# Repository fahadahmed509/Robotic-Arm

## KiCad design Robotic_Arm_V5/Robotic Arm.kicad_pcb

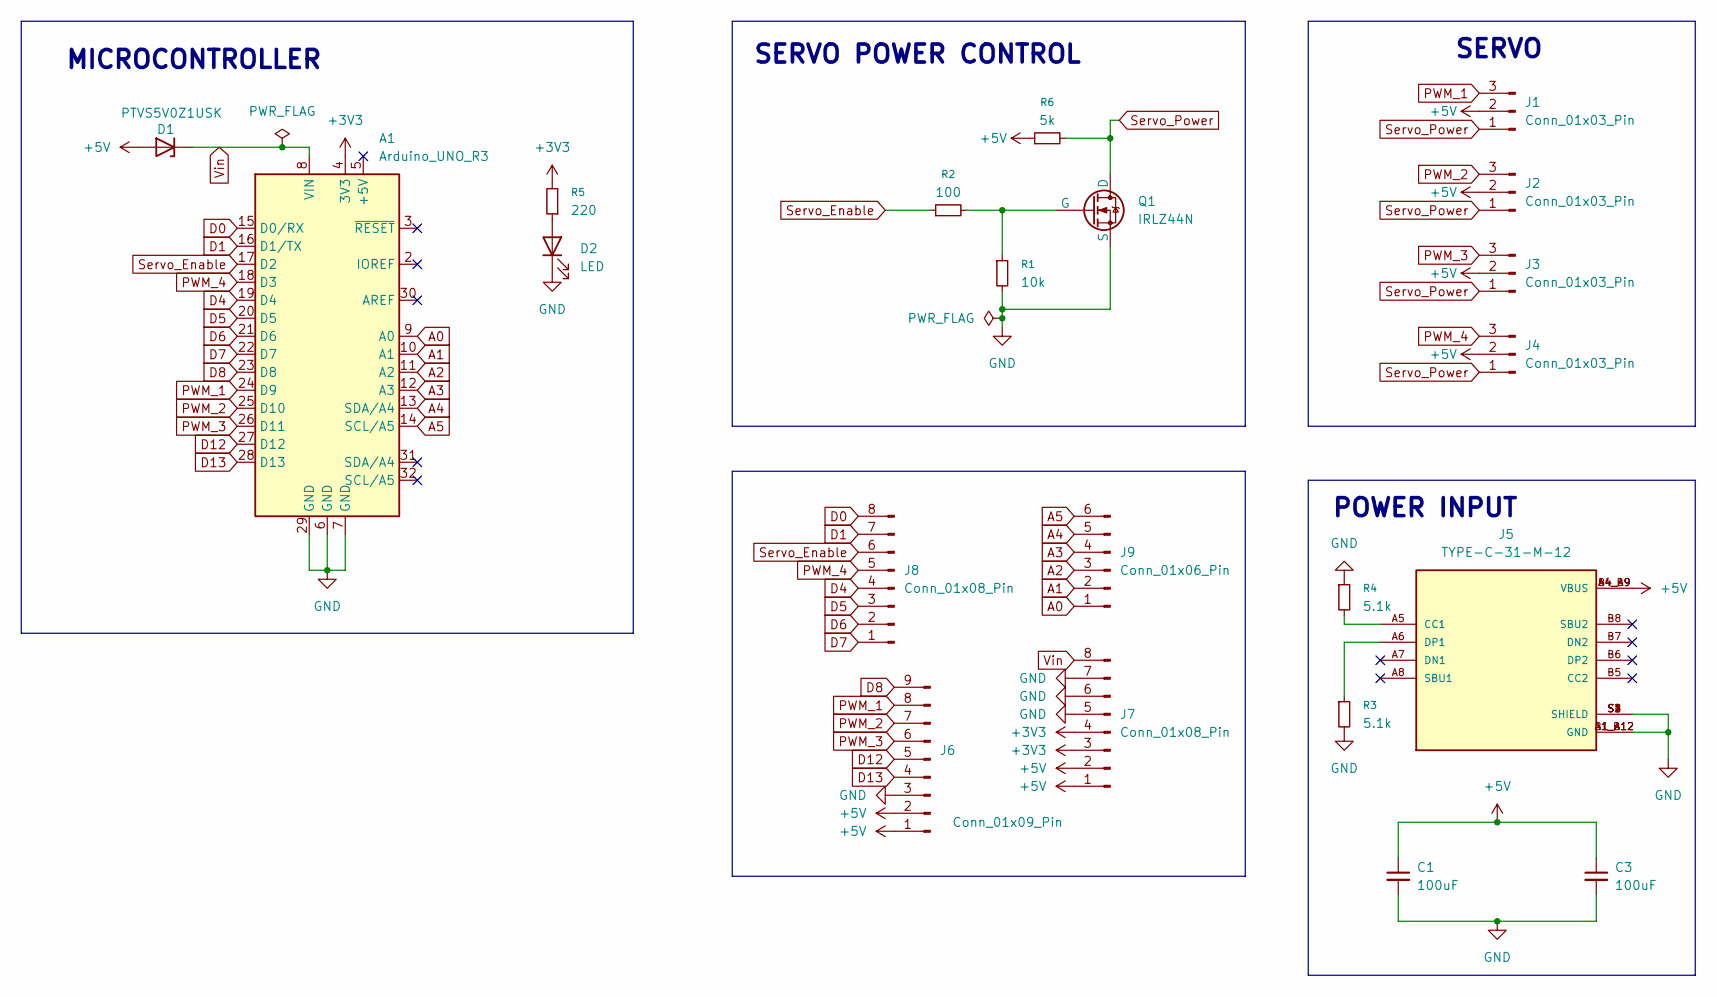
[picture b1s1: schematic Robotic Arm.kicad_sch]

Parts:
A1: Arduino_UNO_R3
C1, C3: 100uF; CP_Radial_D5.0mm_P2.50mm
D1: PTVS5V0Z1USK; D_5W_P10.16mm_Horizontal
D2: LED; LED_D3.0mm
J1, J2, J3, J4: Conn_01x03_Pin; PinHeader_1x03_P2.54mm_Vertical
J5: TYPE-C-31-M-12; HRO_TYPE-C-31-M-12; PARTREV 2020.12.08
J6: Conn_01x09_Pin; PinHeader_1x09_P2.54mm_Vertical
J7, J8: Conn_01x08_Pin; PinHeader_1x08_P2.54mm_Vertical
J9: Conn_01x06_Pin; PinHeader_1x06_P2.54mm_Vertical
Q1: IRLZ44N; TO-220-3_Vertical
R1: 10k; R_Axial_DIN0204_L3.6mm_D1.6mm_P5.08mm_Horizontal
R2: 100; R_Axial_DIN0204_L3.6mm_D1.6mm_P5.08mm_Horizontal
R3, R4: 5.1k; R_Axial_DIN0204_L3.6mm_D1.6mm_P5.08mm_Horizontal
R5: 220; R_Axial_DIN0204_L3.6mm_D1.6mm_P5.08mm_Horizontal
R6: 5k; R_Axial_DIN0204_L3.6mm_D1.6mm_P5.08mm_Horizontal

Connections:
+3V3: A1.4 (3V3), J7.3, J7.4, R5.2
+5V: C1.1, C3.1, D1.2 (A), J1.2, J2.2, J3.2, J4.2, J5.A4_B9 (VBUS), J5.B4_A9 (VBUS), J6.1, J6.2, J7.1, J7.2, R6.1
A0: A1.9 (A0), J9.1
A1: A1.10 (A1), J9.2
A2: A1.11 (A2), J9.3
A3: A1.12 (A3), J9.4
A4: A1.13 (SDA/A4), J9.5
A5: A1.14 (SCL/A5), J9.6
D0: A1.15 (D0/RX), J8.8
D1: A1.16 (D1/TX), J8.7
D4: A1.19 (D4), J8.4
D5: A1.20 (D5), J8.3
D6: A1.21 (D6), J8.2
D7: A1.22 (D7), J8.1
D8: A1.23 (D8), J6.9
D12: A1.27 (D12), J6.5
D13: A1.28 (D13), J6.4
GND: A1.6 (GND), A1.7 (GND), A1.29 (GND), C1.2, C3.2, D2.1 (K), J5.A1_B12 (GND), J5.B1_A12 (GND), J5.S1 (SHIELD), J5.S2 (SHIELD), J5.S3 (SHIELD), J5.S4 (SHIELD), J6.3, J7.5, J7.6, J7.7, Q1.3 (S), R1.2, R3.2, R4.1
unnamed: D2.2 (A), R5.1
unnamed: J5.A5 (CC1), R4.2
unnamed: J5.A6 (DP1), R3.1
unnamed: Q1.1 (G), R1.1, R2.2
PWM_1: A1.24 (D9), J1.3, J6.8
PWM_2: A1.25 (D10), J2.3, J6.7
PWM_3: A1.26 (D11), J3.3, J6.6
PWM_4: A1.18 (D3), J4.3, J8.5
Servo_Enable: A1.17 (D2), J8.6, R2.1
Servo_Power: J1.1, J2.1, J3.1, J4.1, Q1.2 (D), R6.2
Vin: A1.8 (VIN), D1.1 (K), J7.8

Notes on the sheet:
POWER INPUT
MICROCONTROLLER
SERVO
SERVO POWER CONTROL

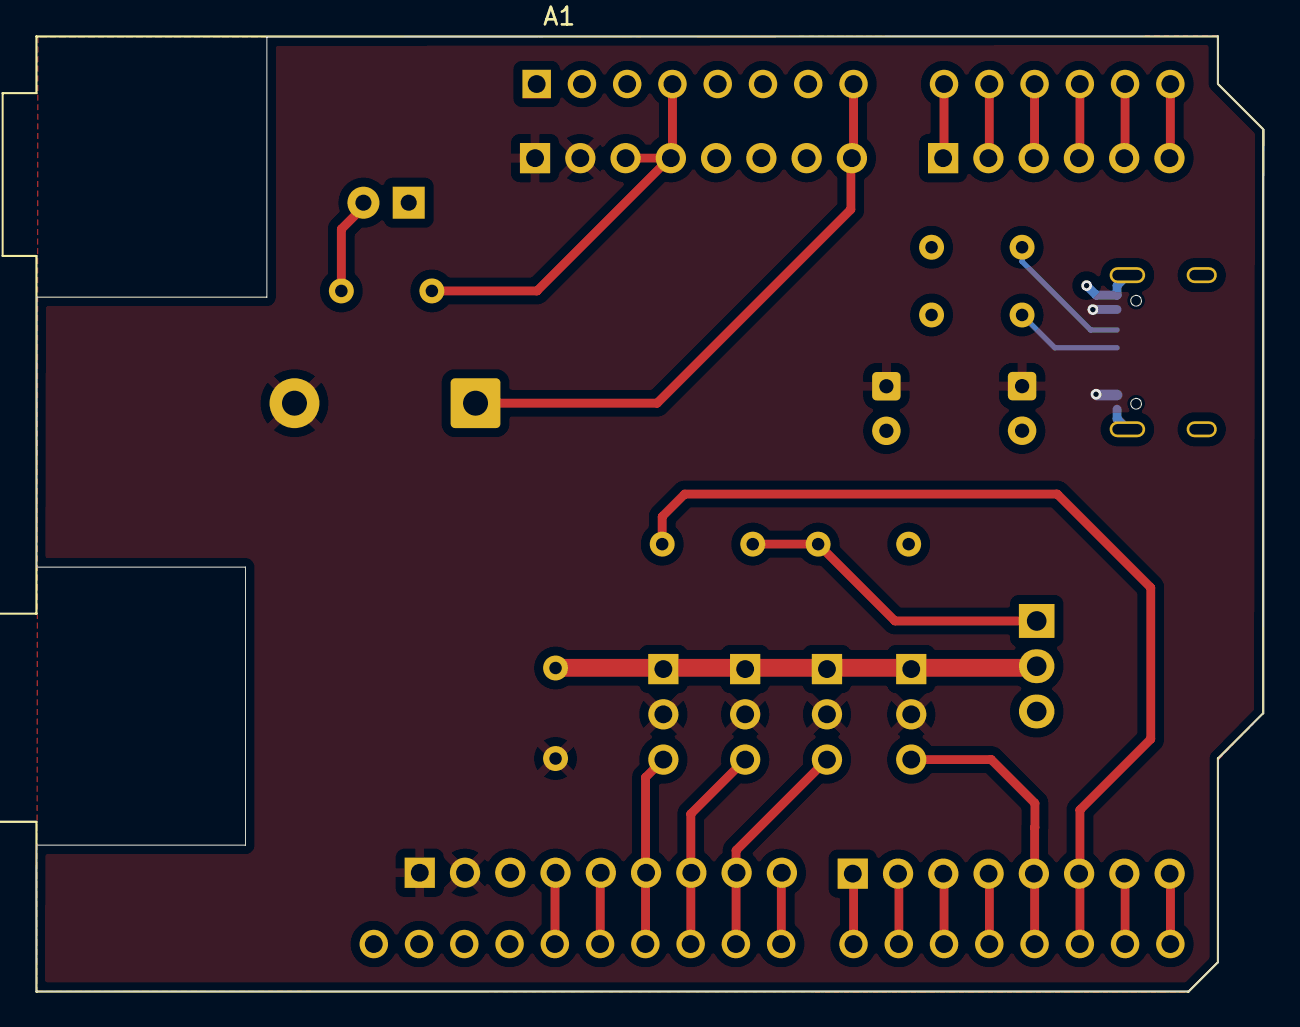
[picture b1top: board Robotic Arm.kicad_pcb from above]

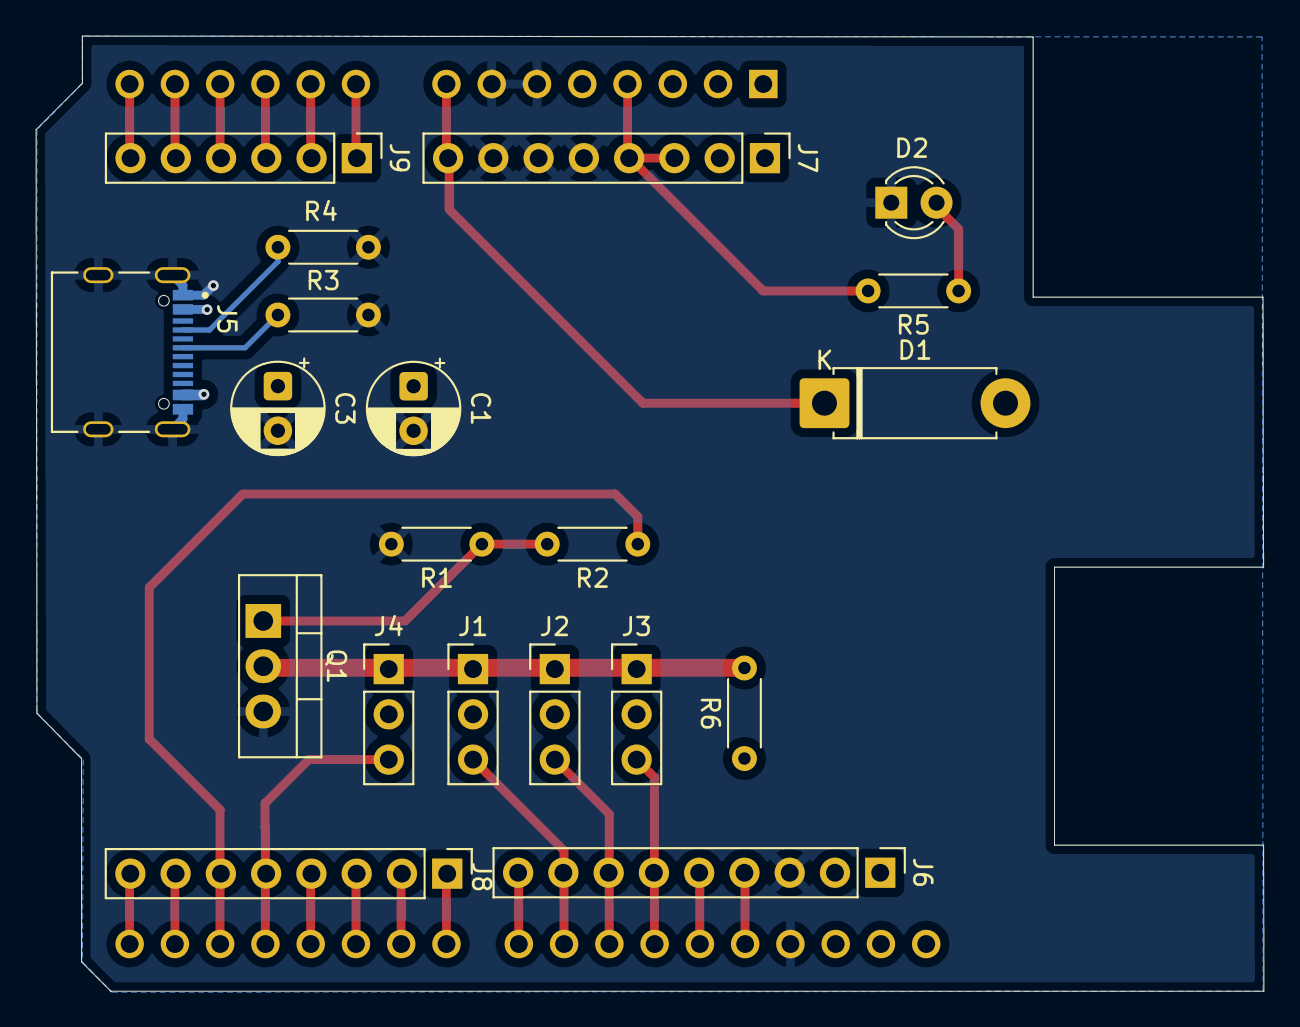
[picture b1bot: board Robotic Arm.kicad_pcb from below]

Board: 2 copper layers, 68.9 x 53.6 mm, 21 parts (20 on the bottom side), 29 nets.

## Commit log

2025-09-18 Added Robotic_Arm_V3 design files
2025-09-23 Added Robotic_Arm_V4 design files
2025-10-24 Fixed MOSFET and Servo Pins
2025-10-24 Add correct Robotic_Arm_V5 folder
2025-10-24 Add Robotic_Arm_V5 folder
